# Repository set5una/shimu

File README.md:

# Project Shimu
I2C/SPI dual protocol ICM-45686/42688P breakout board mechanically compatible with [Adafruit BNO055 breakout](https://www.adafruit.com/product/2472).

> [!WARNING]
> I2C SDA/SCL Pins are exchanged on Shimu compared to the Adafruit BNO055 Pinout.

> [!TIP]
> Supplying 5V to VIN will enable the onboard LDO, which can provide a cleaner power supply to the IMU. The onboard LDO can provide up to 500mA on the 3.3V rail.

## Assembled with TLV75533PDRVR and ICM-45686

## Dimensions in inches (Taken from adafruit BNO055) [^1]

[^1]: https://learn.adafruit.com/adafruit-bno055-absolute-orientation-sensor/downloads

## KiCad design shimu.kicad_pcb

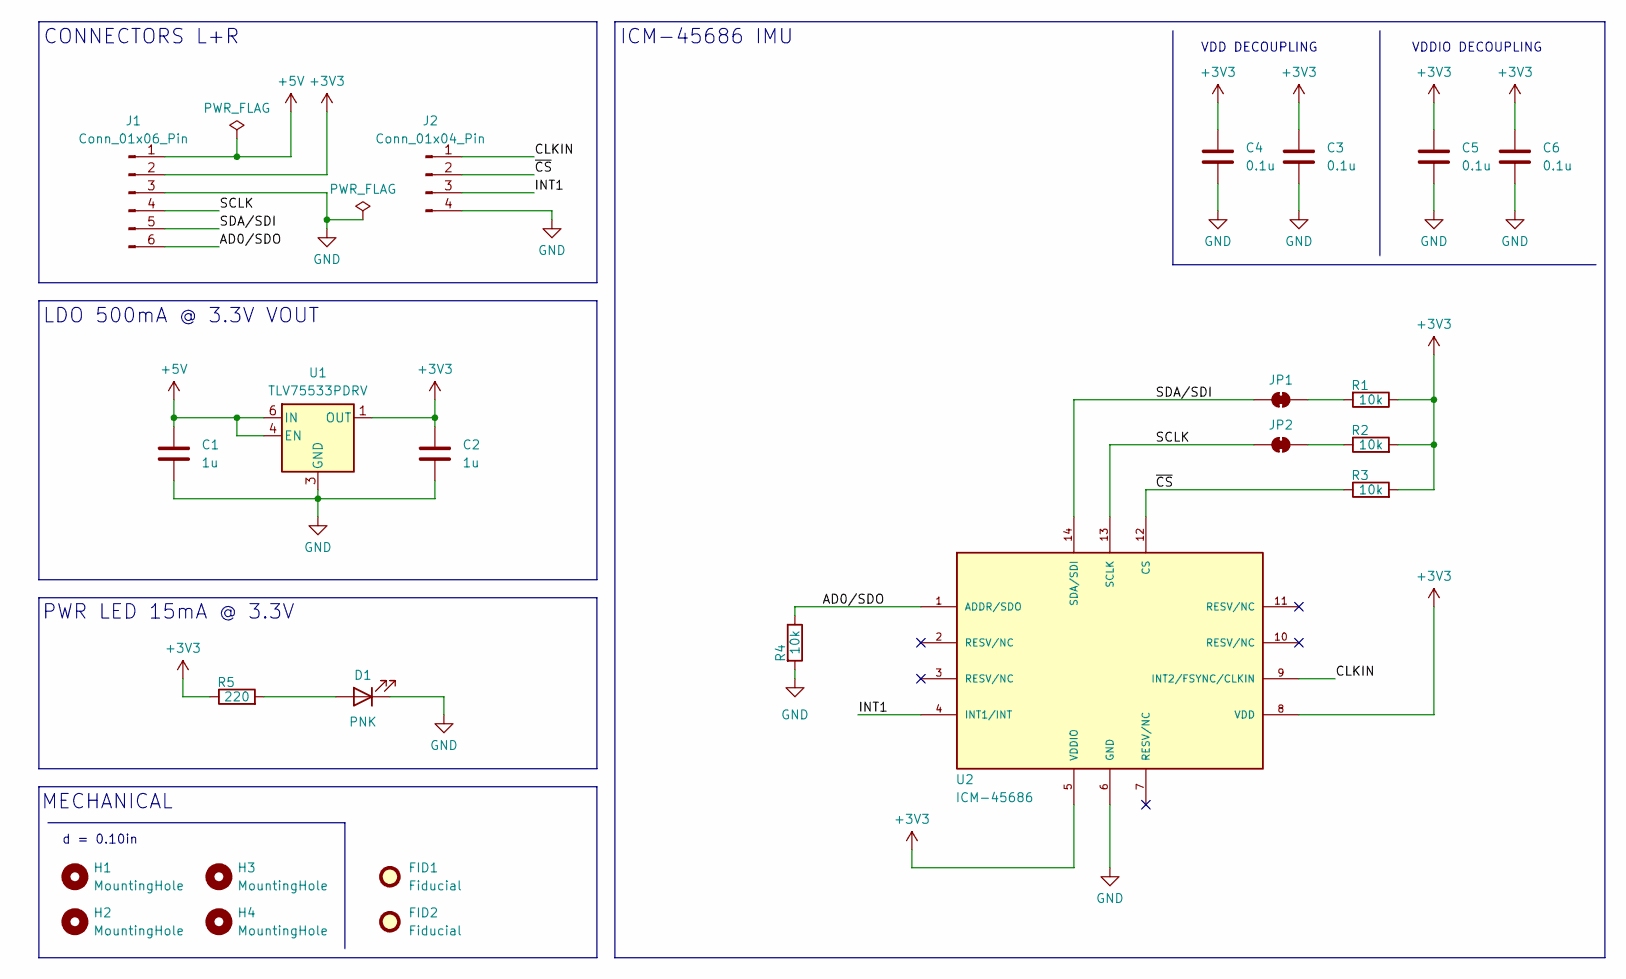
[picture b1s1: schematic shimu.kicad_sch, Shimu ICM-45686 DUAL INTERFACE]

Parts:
C1, C2: 1u; C_0402_1005Metric_Pad0.74x0.62mm_HandSolder
C3, C4, C5, C6: 0.1u; C_0402_1005Metric_Pad0.74x0.62mm_HandSolder
D1: PNK; LED_0603_1608Metric_Pad1.05x0.95mm_HandSolder
FID1, FID2: Fiducial; Fiducial_0.75mm_Mask1.5mm
H1, H2, H3, H4: MountingHole; MountingHole_2.7mm_M2.5
J1: Conn_01x06_Pin; PinHeader_1x06_P2.54mm_Vertical
J2: Conn_01x04_Pin; PinHeader_1x04_P2.54mm_Vertical
JP1, JP2: SolderJumper_2_Bridged; SolderJumper-2_P1.3mm_Bridged_RoundedPad1.0x1.5mm
R1, R2, R3, R4: 10k; R_0402_1005Metric_Pad0.72x0.64mm_HandSolder
R5: 220; R_0402_1005Metric_Pad0.72x0.64mm_HandSolder
U1: TLV75533PDRV; WSON-6-1EP_2x2mm_P0.65mm_EP1x1.6mm
U2: ICM-45686; IC_ICM-45686; PARTREV 0.2

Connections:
+3V3: C2.1, C3.1, C4.1, C5.1, C6.1, J1.2, R1.1, R2.2, R3.2, R5.1, U1.1 (OUT), U2.5 (VDDIO), U2.8 (VDD)
+5V: C1.1, J1.1, U1.4 (EN), U1.6 (IN)
/AD0/SDO: J1.6, R4.1, U2.1 (ADDR/SDO)
/CLKIN: J2.1, U2.9 (INT2/FSYNC/CLKIN)
/INT1: J2.3, U2.4 (INT1/INT)
/SCLK: J1.4, JP2.1 (A), U2.13 (SCLK)
/SDA/SDI: J1.5, JP1.1 (A), U2.14 (SDA/SDI)
/~CS: J2.2, R3.1, U2.12 (CS)
GND: C1.2, C2.2, C3.2, C4.2, C5.2, C6.2, D1.1 (K), J1.3, J2.4, R4.2, U1.2 (NC), U1.3 (GND), U1.5 (NC), U1.7 (GND), U2.6 (GND)
unnamed: D1.2 (A), R5.2
unnamed: JP1.2 (B), R1.2
unnamed: JP2.2 (B), R2.1

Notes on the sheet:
LDO 500mA @ 3.3V VOUT
d = 0.10in
CONNECTORS L+R
MECHANICAL
VDD DECOUPLING
VDDIO DECOUPLING
PWR LED 15mA @ 3.3V
ICM-45686 IMU

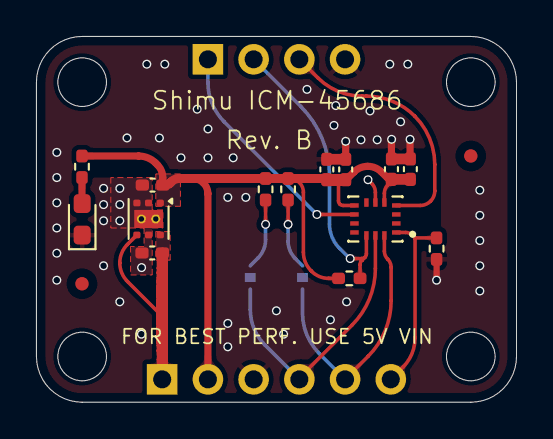
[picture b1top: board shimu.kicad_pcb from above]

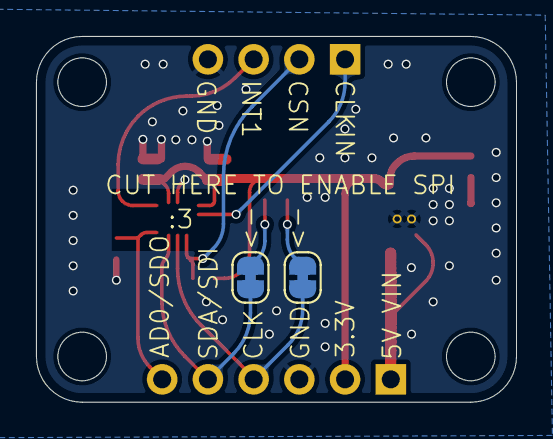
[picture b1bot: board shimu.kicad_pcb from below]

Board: 4 copper layers, 26.7 x 20.3 mm, 24 parts (2 on the bottom side), 12 nets.

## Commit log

2025-10-22 Rev.A
2025-10-27 PCB Rev B: improved ground via placement
2025-11-13 I2C Pinout warning
